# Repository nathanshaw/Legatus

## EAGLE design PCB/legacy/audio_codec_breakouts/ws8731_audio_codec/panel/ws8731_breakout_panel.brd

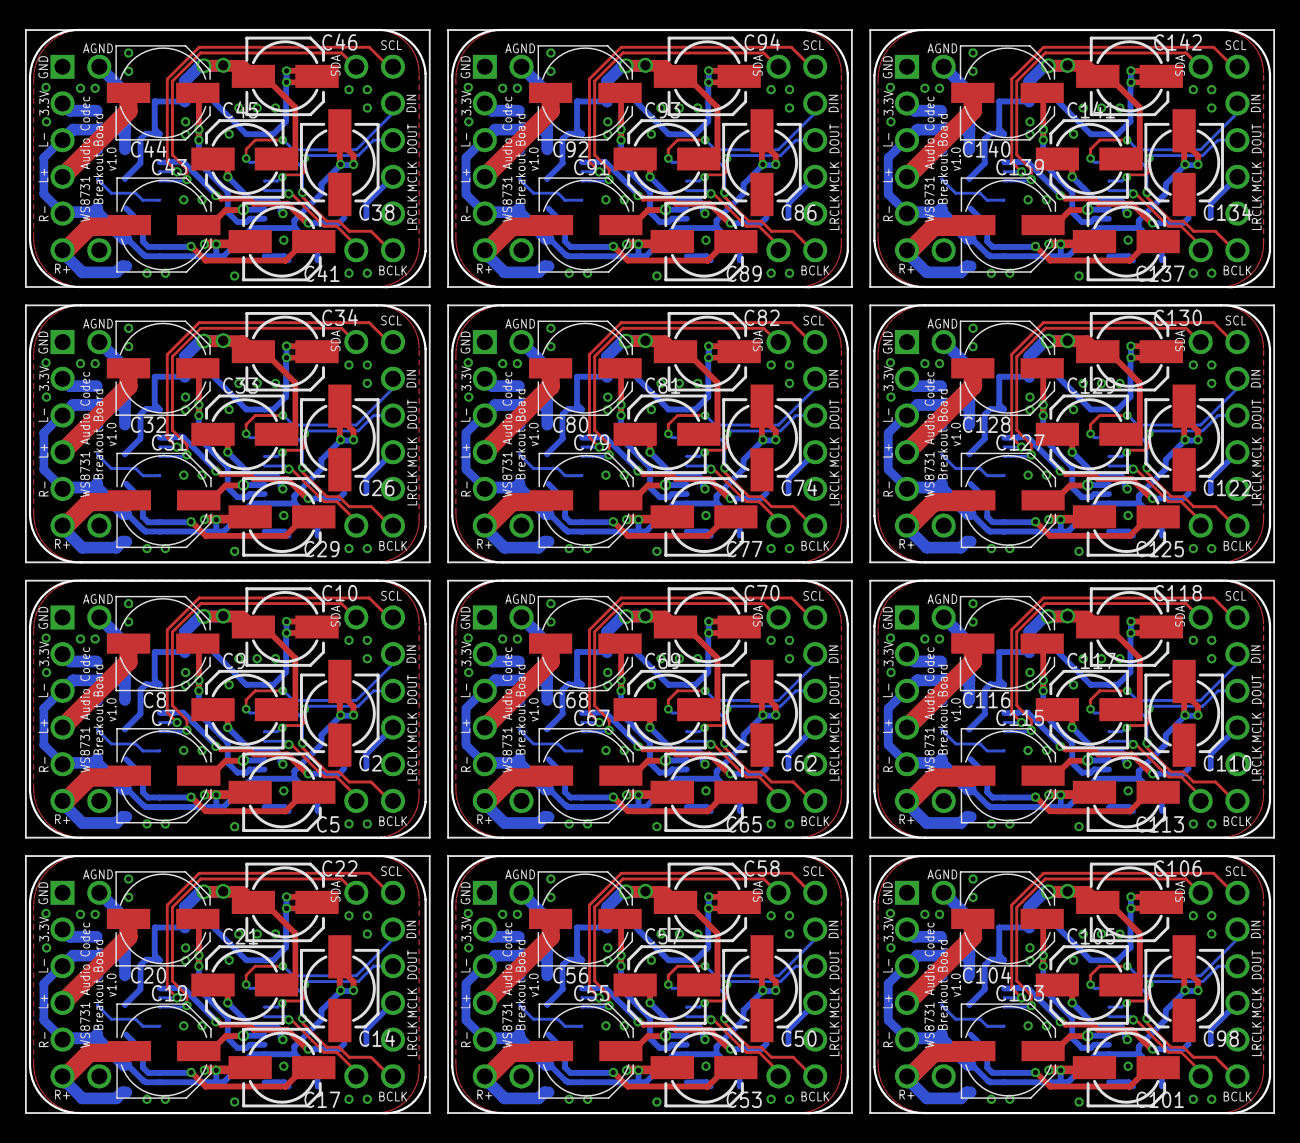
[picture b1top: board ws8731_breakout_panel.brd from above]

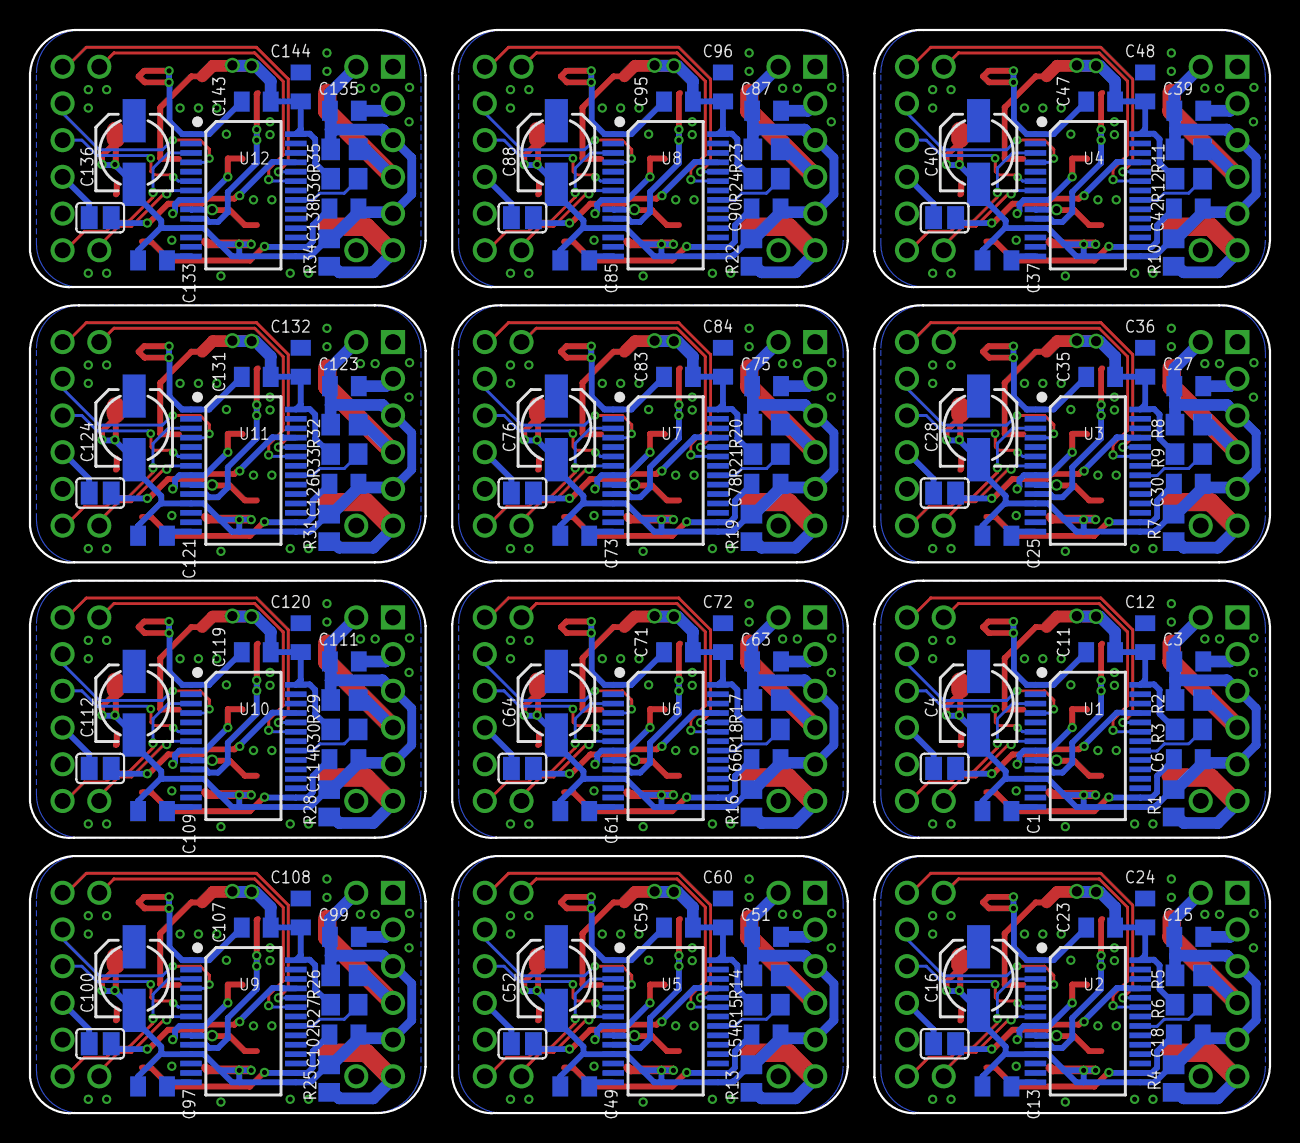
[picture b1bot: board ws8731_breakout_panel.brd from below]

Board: 2 copper layers, 85.8 x 74.9 mm, 216 parts (132 on the bottom side), 216 nets.

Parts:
C1, C3, C6, C11, C12, C13, C15, C18, C23, C24, C25, C27, C30, C35, C36, C37, C39, C42, C47, C48, C49, C51, C54, C59, C60, C61, C63, C66, C71, C72, C73, C75, C78, C83, C84, C85, C87, C90, C95, C96, C97, C99, C102, C107, C108, C109, C111, C114, C119, C120, C121, C123, C126, C131, C132, C133, C135, C138, C143, C144: 0.1uf; C0805K
C2, C4, C5, C9, C10, C14, C16, C17, C21, C22, C26, C28, C29, C33, C34, C38, C40, C41, C45, C46, C50, C52, C53, C57, C58, C62, C64, C65, C69, C70, C74, C76, C77, C81, C82, C86, C88, C89, C93, C94, C98, C100, C101, C105, C106, C110, C112, C113, C117, C118, C122, C124, C125, C129, C130, C134, C136, C137, C141, C142: 10uf; 153CLV-0505
C7, C8, C19, C20, C31, C32, C43, C44, C55, C56, C67, C68, C79, C80, C91, C92, C103, C104, C115, C116, C127, C128, C139, C140: 220uf; PANASONIC_D
R1, R2, R4, R5, R7, R8, R10, R11, R13, R14, R16, R17, R19, R20, R22, R23, R25, R26, R28, R29, R31, R32, R34, R35: 47k; R0805
R3, R6, R9, R12, R15, R18, R21, R24, R27, R30, R33, R36: 10k; R0805
SJ1, SJ2, SJ3, SJ4, SJ5, SJ6, SJ7, SJ8, SJ9, SJ10, SJ11, SJ12: SJ
U1, U2, U3, U4, U5, U6, U7, U8, U9, U10, U11, U12: CODECODER-WM8731SEDS/V(SSOP28); SSOP28-0.65-10.2X5.2MM
U$1, U$2, U$3, U$4, U$5, U$6, U$7, U$8, U$9, U$10, U$11, U$12: AUDIO_CODEC_BREAKOUT; HSS_CODEC_BREAKOUT

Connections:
3.3V: C13.1, C14.+, C15.1, C16.+, C21.+, C24.1, U2.8, U2.14, U2.27, U$12.3.3
3.3V1: C1.1, C2.+, C3.1, C4.+, C9.+, C12.1, U1.8, U1.14, U1.27, U$1.3.3
3.3V2: C25.1, C26.+, C27.1, C28.+, C33.+, C36.1, U3.8, U3.14, U3.27, U$2.3.3
3.3V3: C37.1, C38.+, C39.1, C40.+, C45.+, C48.1, U4.8, U4.14, U4.27, U$3.3.3
3.3V4: C49.1, C50.+, C51.1, C52.+, C57.+, C60.1, U5.8, U5.14, U5.27, U$4.3.3
3.3V5: C61.1, C62.+, C63.1, C64.+, C69.+, C72.1, U6.8, U6.14, U6.27, U$5.3.3
3.3V6: C73.1, C74.+, C75.1, C76.+, C81.+, C84.1, U7.8, U7.14, U7.27, U$6.3.3
3.3V7: C85.1, C86.+, C87.1, C88.+, C93.+, C96.1, U8.8, U8.14, U8.27, U$7.3.3
3.3V8: C97.1, C98.+, C99.1, C100.+, C105.+, C108.1, U9.8, U9.14, U9.27, U$8.3.3
3.3V9: C109.1, C110.+, C111.1, C112.+, C117.+, C120.1, U10.8, U10.14, U10.27, U$9.3.3
3.3V10: C121.1, C122.+, C123.1, C124.+, C129.+, C132.1, U11.8, U11.14, U11.27, U$10.3.3
3.3V11: C133.1, C134.+, C135.1, C136.+, C141.+, C144.1, U12.8, U12.14, U12.27, U$11.3.3
ADCLRCLK: U2.7, U$12.NA2
ADCLRCLK1: U1.7, U$1.NA2
ADCLRCLK2: U3.7, U$2.NA2
ADCLRCLK3: U4.7, U$3.NA2
ADCLRCLK4: U5.7, U$4.NA2
ADCLRCLK5: U6.7, U$5.NA2
ADCLRCLK6: U7.7, U$6.NA2
ADCLRCLK7: U8.7, U$7.NA2
ADCLRCLK8: U9.7, U$8.NA2
ADCLRCLK9: U10.7, U$9.NA2
ADCLRCLK10: U11.7, U$10.NA2
ADCLRCLK11: U12.7, U$11.NA2
AGND: C13.2, C14.-, C15.2, C16.-, C17.-, C18.2, R4.1, R5.1, U2.11, U2.15, U$12.AGND, U$12.LOUT-, U$12.ROUT-
AGND1: C1.2, C2.-, C3.2, C4.-, C5.-, C6.2, R1.1, R2.1, U1.11, U1.15, U$1.AGND, U$1.LOUT-, U$1.ROUT-
AGND2: C25.2, C26.-, C27.2, C28.-, C29.-, C30.2, R7.1, R8.1, U3.11, U3.15, U$2.AGND, U$2.LOUT-, U$2.ROUT-
AGND3: C37.2, C38.-, C39.2, C40.-, C41.-, C42.2, R10.1, R11.1, U4.11, U4.15, U$3.AGND, U$3.LOUT-, U$3.ROUT-
AGND4: C49.2, C50.-, C51.2, C52.-, C53.-, C54.2, R13.1, R14.1, U5.11, U5.15, U$4.AGND, U$4.LOUT-, U$4.ROUT-
AGND5: C61.2, C62.-, C63.2, C64.-, C65.-, C66.2, R16.1, R17.1, U6.11, U6.15, U$5.AGND, U$5.LOUT-, U$5.ROUT-
AGND6: C73.2, C74.-, C75.2, C76.-, C77.-, C78.2, R19.1, R20.1, U7.11, U7.15, U$6.AGND, U$6.LOUT-, U$6.ROUT-
AGND7: C85.2, C86.-, C87.2, C88.-, C89.-, C90.2, R22.1, R23.1, U8.11, U8.15, U$7.AGND, U$7.LOUT-, U$7.ROUT-
AGND8: C97.2, C98.-, C99.2, C100.-, C101.-, C102.2, R25.1, R26.1, U9.11, U9.15, U$8.AGND, U$8.LOUT-, U$8.ROUT-
AGND9: C109.2, C110.-, C111.2, C112.-, C113.-, C114.2, R28.1, R29.1, U10.11, U10.15, U$9.AGND, U$9.LOUT-, U$9.ROUT-
AGND10: C121.2, C122.-, C123.2, C124.-, C125.-, C126.2, R31.1, R32.1, U11.11, U11.15, U$10.AGND, U$10.LOUT-, U$10.ROUT-
AGND11: C133.2, C134.-, C135.2, C136.-, C137.-, C138.2, R34.1, R35.1, U12.11, U12.15, U$11.AGND, U$11.LOUT-, U$11.ROUT-
BCLK: U2.3, U$12.I2S_BCLK
BCLK1: U1.3, U$1.I2S_BCLK
BCLK2: U3.3, U$2.I2S_BCLK
BCLK3: U4.3, U$3.I2S_BCLK
BCLK4: U5.3, U$4.I2S_BCLK
BCLK5: U6.3, U$5.I2S_BCLK
BCLK6: U7.3, U$6.I2S_BCLK
BCLK7: U8.3, U$7.I2S_BCLK
BCLK8: U9.3, U$8.I2S_BCLK
BCLK9: U10.3, U$9.I2S_BCLK
BCLK10: U11.3, U$10.I2S_BCLK
BCLK11: U12.3, U$11.I2S_BCLK
DBVDD: C22.+, C23.1, U2.1
DBVDD1: C10.+, C11.1, U1.1
DBVDD2: C34.+, C35.1, U3.1
DBVDD3: C46.+, C47.1, U4.1
DBVDD4: C58.+, C59.1, U5.1
DBVDD5: C70.+, C71.1, U6.1
DBVDD6: C82.+, C83.1, U7.1
DBVDD7: C94.+, C95.1, U8.1
DBVDD8: C106.+, C107.1, U9.1
DBVDD9: C118.+, C119.1, U10.1
DBVDD10: C130.+, C131.1, U11.1
DBVDD11: C142.+, C143.1, U12.1
DGND: C21.-, C22.-, C23.2, C24.2, R6.1, U2.28
DGND1: C9.-, C10.-, C11.2, C12.2, R3.1, U1.28
DGND2: C33.-, C34.-, C35.2, C36.2, R9.1, U3.28
DGND3: C45.-, C46.-, C47.2, C48.2, R12.1, U4.28
DGND4: C57.-, C58.-, C59.2, C60.2, R15.1, U5.28
DGND5: C69.-, C70.-, C71.2, C72.2, R18.1, U6.28
DGND6: C81.-, C82.-, C83.2, C84.2, R21.1, U7.28
DGND7: C93.-, C94.-, C95.2, C96.2, R24.1, U8.28
DGND8: C105.-, C106.-, C107.2, C108.2, R27.1, U9.28
DGND9: C117.-, C118.-, C119.2, C120.2, R30.1, U10.28
DGND10: C129.-, C130.-, C131.2, C132.2, R33.1, U11.28
DGND11: C141.-, C142.-, C143.2, C144.2, R36.1, U12.28
DIN: U2.4, U$12.I2S_DIN
DIN1: U1.4, U$1.I2S_DIN
DIN2: U3.4, U$2.I2S_DIN
DIN3: U4.4, U$3.I2S_DIN
DIN4: U5.4, U$4.I2S_DIN
DIN5: U6.4, U$5.I2S_DIN
DIN6: U7.4, U$6.I2S_DIN
DIN7: U8.4, U$7.I2S_DIN
DIN8: U9.4, U$8.I2S_DIN
DIN9: U10.4, U$9.I2S_DIN
DIN10: U11.4, U$10.I2S_DIN
DIN11: U12.4, U$11.I2S_DIN
DOUT: U2.6, U$12.I2S_DOUT
DOUT1: U1.6, U$1.I2S_DOUT
DOUT2: U3.6, U$2.I2S_DOUT
DOUT3: U4.6, U$3.I2S_DOUT
DOUT4: U5.6, U$4.I2S_DOUT
DOUT5: U6.6, U$5.I2S_DOUT
DOUT6: U7.6, U$6.I2S_DOUT
DOUT7: U8.6, U$7.I2S_DOUT
DOUT8: U9.6, U$8.I2S_DOUT
DOUT9: U10.6, U$9.I2S_DOUT
DOUT10: U11.6, U$10.I2S_DOUT
DOUT11: U12.6, U$11.I2S_DOUT
I2S_MCLK: SJ2.2, U$12.I2S_MCLK
I2S_MCLK1: SJ1.2, U$1.I2S_MCLK
I2S_MCLK2: SJ3.2, U$2.I2S_MCLK
I2S_MCLK3: SJ4.2, U$3.I2S_MCLK
I2S_MCLK4: SJ5.2, U$4.I2S_MCLK
I2S_MCLK5: SJ6.2, U$5.I2S_MCLK
I2S_MCLK6: SJ7.2, U$6.I2S_MCLK
I2S_MCLK7: SJ8.2, U$7.I2S_MCLK
I2S_MCLK8: SJ9.2, U$8.I2S_MCLK
I2S_MCLK9: SJ10.2, U$9.I2S_MCLK
I2S_MCLK10: SJ11.2, U$10.I2S_MCLK
I2S_MCLK11: SJ12.2, U$11.I2S_MCLK
LHPOUT: C19.+, U2.9
LHPOUT1: C7.+, U1.9
LHPOUT2: C31.+, U3.9
LHPOUT3: C43.+, U4.9
LHPOUT4: C55.+, U5.9
LHPOUT5: C67.+, U6.9
LHPOUT6: C79.+, U7.9
LHPOUT7: C91.+, U8.9
LHPOUT8: C103.+, U9.9
LHPOUT9: C115.+, U10.9
LHPOUT10: C127.+, U11.9
LHPOUT11: C139.+, U12.9
MCLK: SJ2.1, U2.25
MCLK1: SJ1.1, U1.25
MCLK2: SJ3.1, U3.25
MCLK3: SJ4.1, U4.25
MCLK4: SJ5.1, U5.25
MCLK5: SJ6.1, U6.25
MCLK6: SJ7.1, U7.25
MCLK7: SJ8.1, U8.25
MCLK8: SJ9.1, U9.25
MCLK9: SJ10.1, U10.25
MCLK10: SJ11.1, U11.25
MCLK11: SJ12.1, U12.25
MODE1: R6.2, U2.21
MODE2: R3.2, U1.21
MODE3: R9.2, U3.21
MODE4: R12.2, U4.21
MODE5: R15.2, U5.21
MODE6: R18.2, U6.21
MODE7: R21.2, U7.21
MODE8: R24.2, U8.21
MODE9: R27.2, U9.21
MODE10: R30.2, U10.21
MODE11: R33.2, U11.21
MODE12: R36.2, U12.21
unnamed: C5.+, C6.1, U1.16
unnamed: C17.+, C18.1, U2.16
unnamed: C20.-, R5.2, U$12.LOUT+
unnamed: C19.-, R4.2, U$12.ROUT+
unnamed: C8.-, R2.2, U$1.LOUT+
unnamed: C7.-, R1.2, U$1.ROUT+
unnamed: C29.+, C30.1, U3.16
unnamed: C32.-, R8.2, U$2.LOUT+
unnamed: C31.-, R7.2, U$2.ROUT+
unnamed: C41.+, C42.1, U4.16
unnamed: C44.-, R11.2, U$3.LOUT+
unnamed: C43.-, R10.2, U$3.ROUT+
unnamed: C53.+, C54.1, U5.16
unnamed: C56.-, R14.2, U$4.LOUT+
unnamed: C55.-, R13.2, U$4.ROUT+
unnamed: C65.+, C66.1, U6.16
unnamed: C68.-, R17.2, U$5.LOUT+
unnamed: C67.-, R16.2, U$5.ROUT+
unnamed: C77.+, C78.1, U7.16
unnamed: C80.-, R20.2, U$6.LOUT+
unnamed: C79.-, R19.2, U$6.ROUT+
unnamed: C89.+, C90.1, U8.16
unnamed: C92.-, R23.2, U$7.LOUT+
unnamed: C91.-, R22.2, U$7.ROUT+
unnamed: C101.+, C102.1, U9.16
unnamed: C104.-, R26.2, U$8.LOUT+
unnamed: C103.-, R25.2, U$8.ROUT+
unnamed: C113.+, C114.1, U10.16
unnamed: C116.-, R29.2, U$9.LOUT+
unnamed: C115.-, R28.2, U$9.ROUT+
unnamed: C125.+, C126.1, U11.16
unnamed: C128.-, R32.2, U$10.LOUT+
unnamed: C127.-, R31.2, U$10.ROUT+
unnamed: C137.+, C138.1, U12.16
unnamed: C140.-, R35.2, U$11.LOUT+
unnamed: C139.-, R34.2, U$11.ROUT+
RHPOUT: C20.+, U2.10
RHPOUT1: C8.+, U1.10
RHPOUT2: C32.+, U3.10
RHPOUT3: C44.+, U4.10
RHPOUT4: C56.+, U5.10
RHPOUT5: C68.+, U6.10
RHPOUT6: C80.+, U7.10
RHPOUT7: C92.+, U8.10
RHPOUT8: C104.+, U9.10
RHPOUT9: C116.+, U10.10
RHPOUT10: C128.+, U11.10
RHPOUT11: C140.+, U12.10
SCL: U2.24, U$12.SCL
SCL1: U1.24, U$1.SCL
SCL2: U3.24, U$2.SCL
SCL3: U4.24, U$3.SCL
SCL4: U5.24, U$4.SCL
SCL5: U6.24, U$5.SCL
SCL6: U7.24, U$6.SCL
SCL7: U8.24, U$7.SCL
SCL8: U9.24, U$8.SCL
SCL9: U10.24, U$9.SCL
SCL10: U11.24, U$10.SCL
SCL11: U12.24, U$11.SCL
SDA: U2.23, U$12.SDA
SDA1: U1.23, U$1.SDA
SDA2: U3.23, U$2.SDA
SDA3: U4.23, U$3.SDA
SDA4: U5.23, U$4.SDA
SDA5: U6.23, U$5.SDA
SDA6: U7.23, U$6.SDA
SDA7: U8.23, U$7.SDA
SDA8: U9.23, U$8.SDA
SDA9: U10.23, U$9.SDA
SDA10: U11.23, U$10.SDA
SDA11: U12.23, U$11.SDA

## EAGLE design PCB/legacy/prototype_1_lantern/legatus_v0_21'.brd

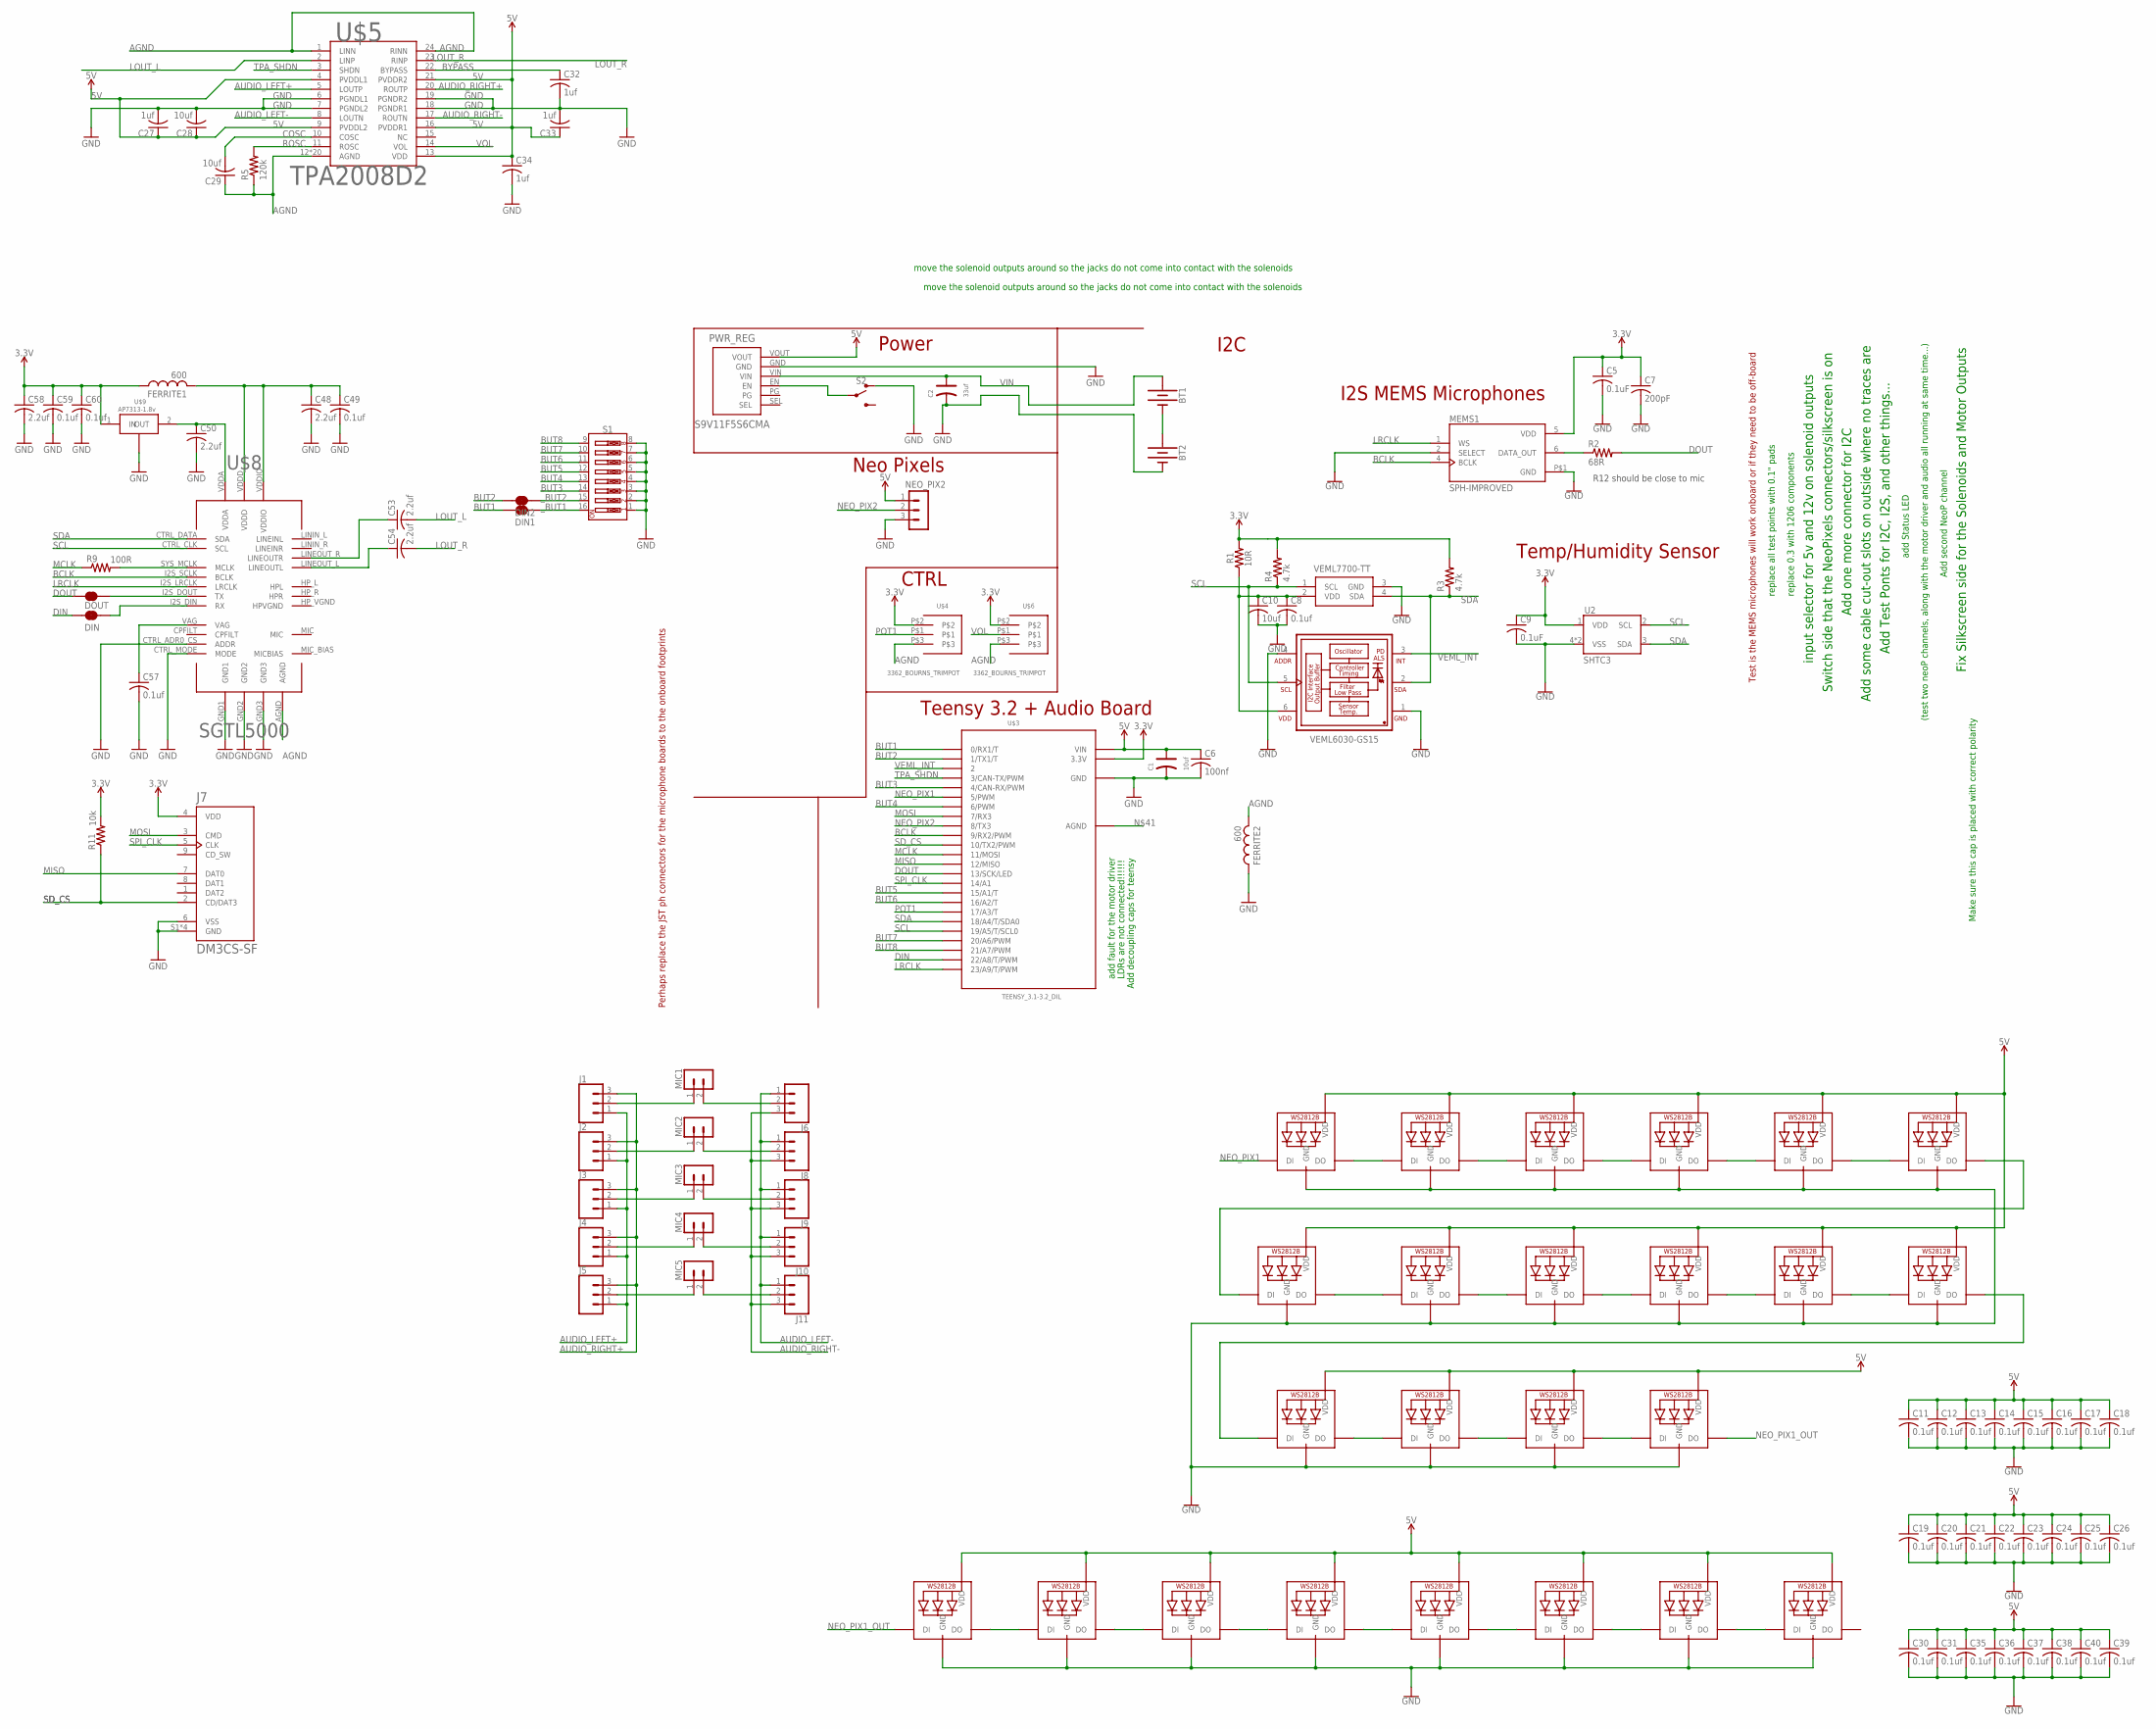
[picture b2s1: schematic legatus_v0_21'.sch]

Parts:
BT1, BT2: BATTERY-18650; BATTERY_18650-HOLDER
C1: 10uf; PC-D5.3MM
C2: 33uf; PC-D5.3MM
C5, C9: 0.1uF; C0805
C6: 100nf; C2012
C7: 200pF; C0805
C8, C11, C12, C13, C14, C15, C16, C17, C18, C19, C20, C21, C22, C23, C24, C25, C26, C30, C31, C35, C36, C37, C38, C39, C40, C49, C57, C59, C60: 0.1uf; C0805
C10, C28, C29: 10uf; C0805
C27, C32, C33, C34: 1uf; C0805
C48, C50, C53, C54, C58: 2.2uf; C0805
DIN, DIN1, DIN2: JUMPER-SMT_2_NC_TRACE_SILK; SMT-JUMPER_2_NC_TRACE_SILK
DOUT: JUMPER-SMT_2_NC_TRACE_SILK; SMT-JUMPER_2_NC_TRACE_SILK
FERRITE1, FERRITE2: 600; RESC0805_N
J1, J2, J3, J4, J5, J6, J8, J9, J10, J11: CONN_03; 1X03
J7: DM3CS-SF; HRS_DM3CS-SF
LED1, LED2, LED3, LED4, LED5, LED6, LED7, LED8, LED9, LED10, LED11, LED12, LED13, LED14, LED15, LED16, LED17, LED18, LED19, LED20, LED21, LED22, LED23, LED24: WS2812B_5050N; WS2812B-NARROW
MEMS1: SPH-IMPROVED; MIC_SPH0645LM4H-B_LARGER_RING
MIC1, MIC2, MIC3, MIC4, MIC5: B2B-PH-K
NEO_PIX2: B3B-PH-K
PWR_REG: S9V11F5S6CMA; S9V11F3S5CMA
R1: 10R; R0805
R2: 68R; M0805
R3, R4: 4.7k; M0805
R5: 120k; M0805
R9: 100R; M0805
R11: 10k; M0805
S1: DIP-08-PTH; DIPSWITCH-08
S2: SWITCH-SPDT-PTH-11.6X4.0MM-LOCK; SWITCH_SPDT_PTH_11.6X4.0MM_LOCK
U2: SHTC3
U$3: TEENSY_3.1-3.2_DIL; TEENSY_3.0-3.2&LC_DIL
U$4, U$6: 3362_BOURNS_TRIMPOT
U$5: TPA2008D2; PWP-TSSOP24
U$8: SGTL5000; QFN-32-5X5MM
U$9: AP7313-1.8v; SOT-23
VEML1: VEML7700-TT; VEML7700
VMEL1: VEML6030-GS15; VISHAY_VEML6030_2X2X0.87

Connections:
3.3V: C5.1, C7.1, C9.1, C58.1, C59.1, C60.1, FERRITE1.1, J7.4 (VDD), MEMS1.5 (VDD), R1.2, R3.2, R4.2, R11.2, U2.1 (VDD), U$3.3.3V, U$4.P$2, U$6.P$2, U$9.1 (IN)
5V: C1.+, C6.1, C11.1, C12.1, C13.1, C14.1, C15.1, C16.1, C17.1, C18.1, C19.1, C20.1, C21.1, C22.1, C23.1, C24.1, C25.1, C26.1, C27.1, C28.1, C30.1, C31.1, C33.1, C34.1, C35.1, C36.1, C37.1, C38.1, C39.1, C40.1, LED1.1-VDD (VDD), LED2.1-VDD (VDD), LED3.1-VDD (VDD), LED4.1-VDD (VDD), LED5.1-VDD (VDD), LED6.1-VDD (VDD), LED7.1-VDD (VDD), LED8.1-VDD (VDD), LED9.1-VDD (VDD), LED10.1-VDD (VDD), LED11.1-VDD (VDD), LED12.1-VDD (VDD), LED13.1-VDD (VDD), LED14.1-VDD (VDD), LED15.1-VDD (VDD), LED16.1-VDD (VDD), LED17.1-VDD (VDD), LED18.1-VDD (VDD), LED19.1-VDD (VDD), LED20.1-VDD (VDD), LED21.1-VDD (VDD), LED22.1-VDD (VDD), LED23.1-VDD (VDD), LED24.1-VDD (VDD), NEO_PIX2.1, PWR_REG.VOUT, U$3.VIN, U$5.4 (PVDDL1), U$5.9 (PVDDL2), U$5.13 (VDD), U$5.16 (PVDDR1), U$5.21 (PVDDR2)
AGND: C29.1, FERRITE2.2, R5.1, U$4.P$3, U$5.1 (LINN), U$5.12 (AGND), U$5.24 (RINN), U$5.EXP (AGND), U$5.EXP@1 (AGND), U$5.EXP@2 (AGND), U$5.EXP@3 (AGND), U$5.EXP@4 (AGND), U$5.EXP@5 (AGND), U$5.EXP@6 (AGND), U$5.EXP@7 (AGND), U$5.EXP@8 (AGND), U$5.EXP@9 (AGND), U$5.EXP@10 (AGND), U$5.EXP@11 (AGND), U$5.EXP@12 (AGND), U$5.EXP@13 (AGND), U$5.EXP@14 (AGND), U$5.EXP@15 (AGND), U$5.EXP@16 (AGND), U$5.EXP@17 (AGND), U$5.EXP@18 (AGND), U$6.P$3, U$8.AGND
AUDIO_LEFT+: J1.1, J2.1, J3.1, J4.1, J5.1, U$5.5 (LOUTP)
AUDIO_LEFT-: J6.1, J8.1, J9.1, J10.1, J11.1, U$5.8 (LOUTN)
AUDIO_RIGHT+: J1.3, J2.3, J3.3, J4.3, J5.3, U$5.20 (ROUTP)
AUDIO_RIGHT-: J6.3, J8.3, J9.3, J10.3, J11.3, U$5.17 (ROUTN)
BCLK: MEMS1.4 (BCLK), U$3.9 (9/RX2/PWM), U$8.I2S_SCLK (BCLK)
BUT1: DIN1.1, U$3.0 (0/RX1/T)
BUT2: DIN2.1, U$3.1 (1/TX1/T)
BUT3: S1.14, U$3.4 (4/CAN-RX/PWM)
BUT4: S1.13, U$3.6 (6/PWM)
BUT5: S1.12, U$3.15/A1 (15/A1/T)
BUT6: S1.11, U$3.16/A2 (16/A2/T)
BUT7: S1.10, U$3.20/A6 (20/A6/PWM)
BUT8: S1.9, U$3.21/A7 (21/A7/PWM)
BYPASS: C32.1, U$5.22 (BYPASS)
COSC: C29.2, U$5.10 (COSC)
DIN: DIN.1, U$3.22/A8 (22/A8/T/PWM)
DOUT: DOUT.1, R2.2, U$3.13 (13/SCK/LED)
EDITROUTE: C48.1, C49.1, FERRITE1.2, U$8.VDDD, U$8.VDDIO
GND: BT2.GND@1 (-), C1.-, C2.-, C5.2, C6.2, C7.2, C8.2, C9.2, C10.2, C11.2, C12.2, C13.2, C14.2, C15.2, C16.2, C17.2, C18.2, C19.2, C20.2, C21.2, C22.2, C23.2, C24.2, C25.2, C26.2, C27.2, C28.2, C30.2, C31.2, C32.2, C33.2, C34.2, C35.2, C36.2, C37.2, C38.2, C39.2, C40.2, C48.2, C49.2, C50.2, C57.2, C58.2, C59.2, C60.2, FERRITE2.1, J7.6 (VSS), J7.S1 (GND), J7.S2 (GND), J7.S3 (GND), J7.S5 (GND), LED1.3-GND (GND), LED2.3-GND (GND), LED3.3-GND (GND), LED4.3-GND (GND), LED5.3-GND (GND), LED6.3-GND (GND), LED7.3-GND (GND), LED8.3-GND (GND), LED9.3-GND (GND), LED10.3-GND (GND), LED11.3-GND (GND), LED12.3-GND (GND), LED13.3-GND (GND), LED14.3-GND (GND), LED15.3-GND (GND), LED16.3-GND (GND), LED17.3-GND (GND), LED18.3-GND (GND), LED19.3-GND (GND), LED20.3-GND (GND), LED21.3-GND (GND), LED22.3-GND (GND), LED23.3-GND (GND), LED24.3-GND (GND), MEMS1.2 (SELECT), MEMS1.P$1 (GND), NEO_PIX2.3, PWR_REG.GND, S1.1, S1.2, S1.3, S1.4, S1.5, S1.6, S1.7, S1.8, S2.1 (O), U2.4 (VSS), U2.5 (VSS), U$3.GND, U$5.6 (PGNDL1), U$5.7 (PGNDL2), U$5.18 (PGNDR1), U$5.19 (PGNDR2), U$8.CTRL_ADR0_CS (ADDR), U$8.CTRL_MODE (MODE), U$8.GND1, U$8.GND2, U$8.GND3, U$9.3 (GND), VEML1.3 (GND), VMEL1.1 (GND), VMEL1.4 (ADDR)
LOUT_L: C53.2, U$5.2 (LINP)
LOUT_R: C54.2, U$5.23 (RINP)
LRCLK: MEMS1.1 (WS), U$3.23/A9 (23/A9/T/PWM), U$8.I2S_LRCLK (LRCLK)
MCLK: R9.1, U$3.11 (11/MOSI)
MISO: J7.7 (DAT0), U$3.12 (12/MISO)
MOSI: J7.3 (CMD), U$3.7 (7/RX3)
unnamed: MEMS1.6 (DATA_OUT), R2.1
unnamed: J1.2, MIC1.1
unnamed: J2.2, MIC2.1
unnamed: C8.1, C10.1, R1.1, VEML1.2 (VDD), VMEL1.6 (VDD)
unnamed: PWR_REG.EN, S2.2
unnamed: J3.2, MIC3.1
unnamed: J4.2, MIC4.1
unnamed: J5.2, MIC5.1
unnamed: LED1.2-DOUT (DO), LED2.4-DIN (DI)
unnamed: LED2.2-DOUT (DO), LED3.4-DIN (DI)
unnamed: LED3.2-DOUT (DO), LED4.4-DIN (DI)
unnamed: LED4.2-DOUT (DO), LED5.4-DIN (DI)
unnamed: LED5.2-DOUT (DO), LED6.4-DIN (DI)
unnamed: LED7.2-DOUT (DO), LED8.4-DIN (DI)
unnamed: LED8.2-DOUT (DO), LED9.4-DIN (DI)
unnamed: LED9.2-DOUT (DO), LED10.4-DIN (DI)
unnamed: LED10.2-DOUT (DO), LED11.4-DIN (DI)
unnamed: LED11.2-DOUT (DO), LED12.4-DIN (DI)
unnamed: LED13.2-DOUT (DO), LED14.4-DIN (DI)
unnamed: LED14.2-DOUT (DO), LED15.4-DIN (DI)
unnamed: LED15.2-DOUT (DO), LED16.4-DIN (DI)
unnamed: BT1.GND@1 (-), BT2.PWR@1 (+)
unnamed: LED12.2-DOUT (DO), LED13.4-DIN (DI)
unnamed: LED6.2-DOUT (DO), LED7.4-DIN (DI)
unnamed: J6.2, MIC1.2
unnamed: LED18.2-DOUT (DO), LED19.4-DIN (DI)
unnamed: C53.1, U$8.LINEOUT_R (LINEOUTR)
unnamed: C54.1, U$8.LINEOUT_L (LINEOUTL)
unnamed: LED19.2-DOUT (DO), LED20.4-DIN (DI)
unnamed: LED20.2-DOUT (DO), LED21.4-DIN (DI)
unnamed: LED21.2-DOUT (DO), LED22.4-DIN (DI)
unnamed: J8.2, MIC2.2
unnamed: LED22.2-DOUT (DO), LED23.4-DIN (DI)
unnamed: C57.1, U$8.VAG
unnamed: DIN.2, U$8.I2S_DIN (RX)
unnamed: DOUT.2, U$8.I2S_DOUT (TX)
unnamed: LED23.2-DOUT (DO), LED24.4-DIN (DI)
unnamed: R9.2, U$8.SYS_MCLK (MCLK)
unnamed: C50.1, U$8.VDDA, U$9.2 (OUT)
unnamed: J9.2, MIC3.2
unnamed: J10.2, MIC4.2
unnamed: LED17.2-DOUT (DO), LED18.4-DIN (DI)
unnamed: J11.2, MIC5.2
NEO_PIX1: LED1.4-DIN (DI), U$3.5 (5/PWM)
NEO_PIX1_OUT: LED16.2-DOUT (DO), LED17.4-DIN (DI)
NEO_PIX2: NEO_PIX2.2, U$3.8 (8/TX3)
POT1: U$3.17/A3 (17/A3/T), U$4.P$1
ROSC: R5.2, U$5.11 (ROSC)
SCL: R4.1, U2.2 (SCL), U$3.19/A5 (19/A5/T/SCL0), U$8.CTRL_CLK (SCL), VEML1.1 (SCL), VMEL1.5 (SCL)
SDA: R3.1, U2.3 (SDA), U$3.18/A4 (18/A4/T/SDA0), U$8.CTRL_DATA (SDA), VEML1.4 (SDA), VMEL1.2 (SDA)
SD_CS: J7.2 (CD/DAT3), R11.1, U$3.10 (10/TX2/PWM)
SPI_CLK: J7.5 (CLK), U$3.14/A0 (14/A1)
TPA_SHDN: U$3.3 (3/CAN-TX/PWM), U$5.3 (SHDN)
VEML_INT: U$3.2, VMEL1.3 (INT)
VIN: BT1.PWR@1 (+), C2.+, PWR_REG.VIN
VOL: U$5.14 (VOL), U$6.P$1
_BUT1: DIN1.2, S1.16
_BUT2: DIN2.2, S1.15

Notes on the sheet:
Neo Pixels
I2C
Teensy 3.2 + Audio Board
Power
Make sure this cap is placed with correct polarity
CTRL
add fault for the motor driver
LDRs are not connected!!!!!!
Fix Silkscreen side for the Solenoids and Motor Outputs
Add Test Ponts for I2C, I2S, and other things...
Add some cable cut-out slots on outside where no traces are
Add one more connector for I2C
Switch side that the NeoPixels connectors/silkscreen is on
input selector for 5v and 12v on solenoid outputs
Add second NeoP channel
(test two neoP channels, along with the motor driver and audio all running at same time...)
add Status LED
replace 0.3 with 1206 components
replace all test points with 0.1" pads
Add decoupling caps for teensy
Test is the MEMS microphones will work onboard or if they need to be off-board
Perhaps replace the JST ph connectors for the microphone boards to the onboard footprints
move the solenoid outputs around so the jacks do not come into contact with the solenoids
I2S MEMS Microphones
R12 should be close to mic
Temp/Humidity Sensor
10R

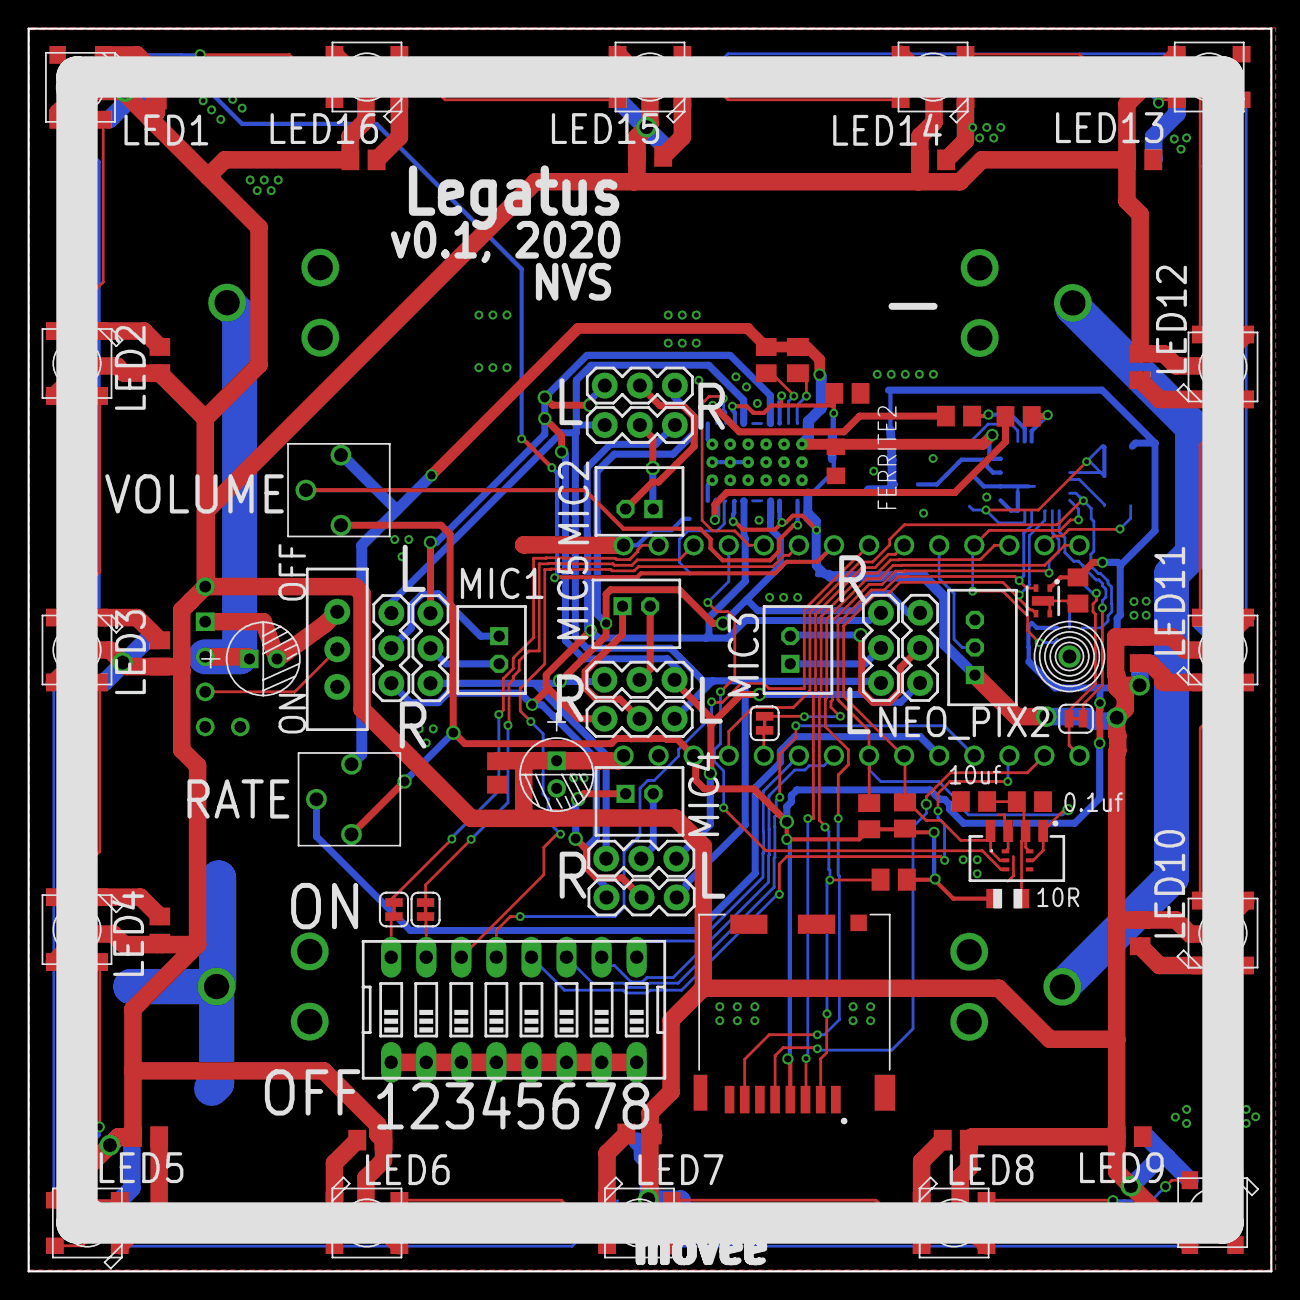
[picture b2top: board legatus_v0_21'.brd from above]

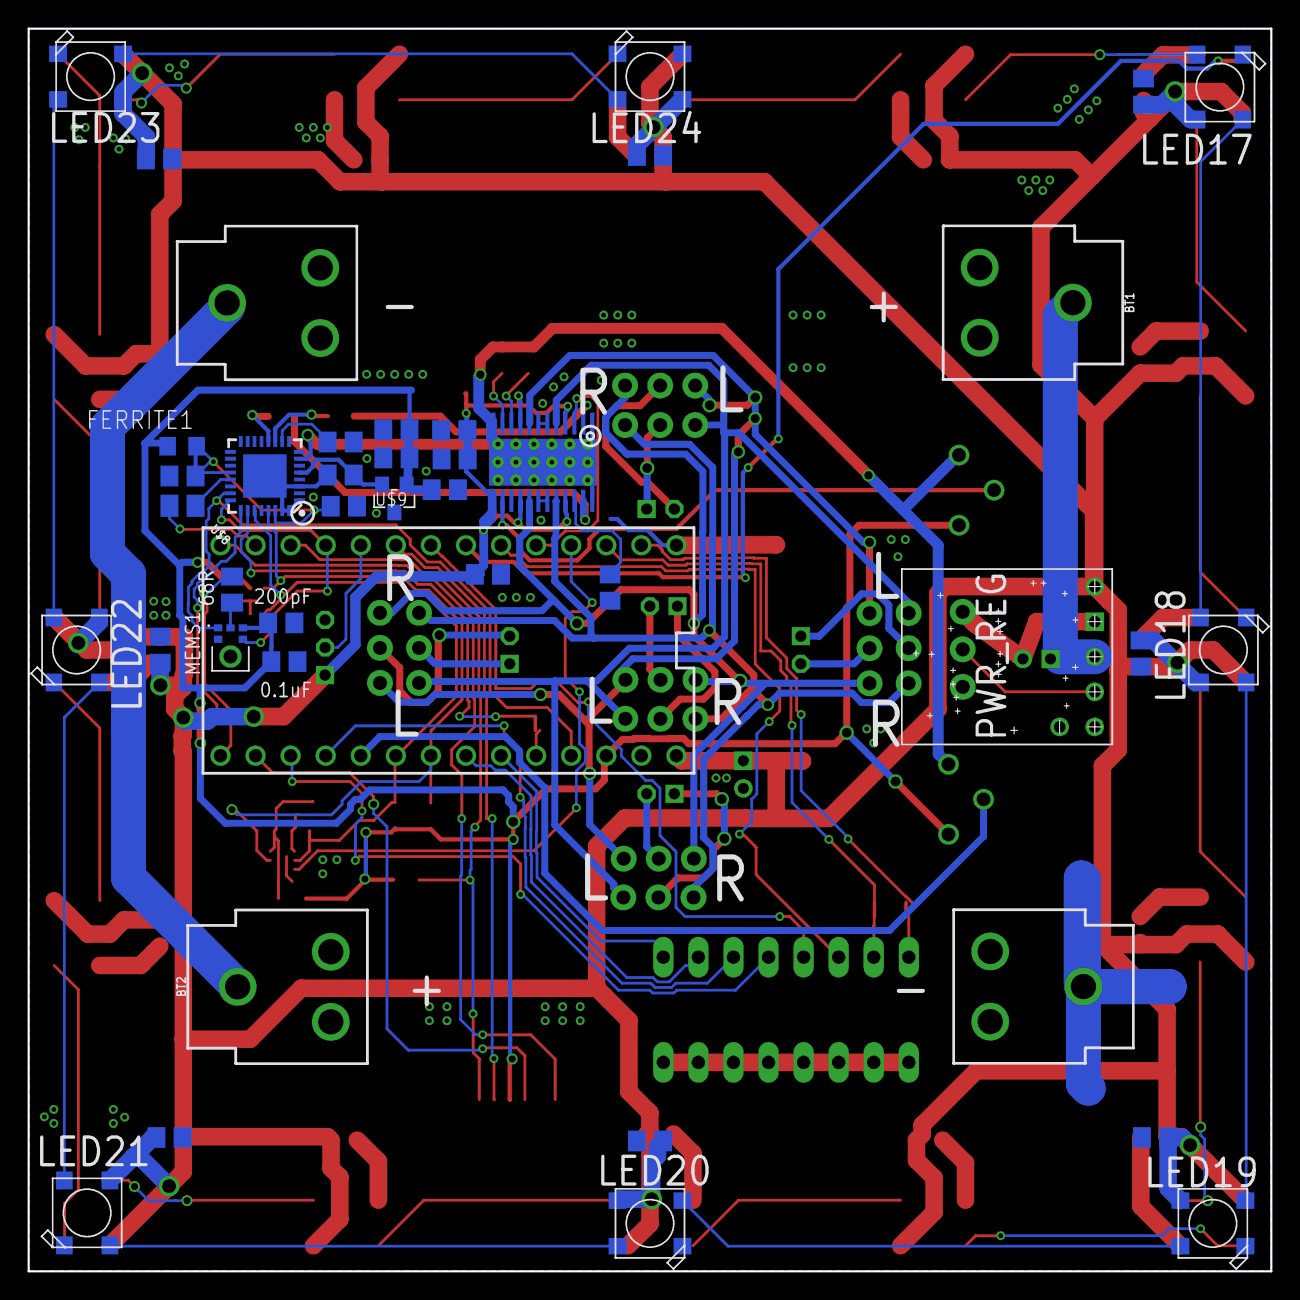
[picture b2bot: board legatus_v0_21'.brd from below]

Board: 2 copper layers, 90.0 x 90.0 mm, 116 parts (40 on the bottom side), 86 nets.

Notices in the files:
parts and their libraries:
SparkFun-Capacitors: Licensing: Creative Commons ShareAlike 4.0 International - https://creativecommons.org/licenses/by-sa/4.0
con-jst-ph: Copyright (C) 2016, Bob Starr
